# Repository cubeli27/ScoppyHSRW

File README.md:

# Scoppy 

## Overview
Scoppy is an hardware extension project designed to be compatible with the [original Scopy Project](https://github.com/fhdm-dev/scoppy) developed by fhdm-dev. This repository extends the original Raspberry Pi Pico oscilloscope software by providing custom hardware developed as teaching material for the course Design and Manufacturing of Electronics.

The hardware platform enables students to study and manufacture a complete measurement instrument while using the original Scoppy firmware.

<!-- To-do: Add more photos to the list -->

Key Features
- Oscilloscope
- Logic analyzer
- Function generator

---

## Project Structure

| Folder | Description | Contents |
|--------|-------------|-------------|
| **CAD_files** | Case drawings and pcb | .pdf and .step |
| **ECAD_files** | Contains PCB files | Original design and student template  |
| **Images** | Report relevant snippets | Images |
| **Waveforms** | Waveforms Testing Workspace | .dwf3work |

---

## Testing

Images of Scoppy in action.

---
## Firmware

Original project can be found at:<br>
[Github](https://github.com/fhdm-dev/scoppy)<br>
[EasyEDA](https://easyeda.com/editor#id=5d5f637d6a8448b59f484372ed679191)<br>
[Website](https://oscilloscope.fhdm.xyz/)  
 
---
## Getting Started

From the [Scoppy Firmware downloads](https://oscilloscope.fhdm.xyz/wiki/firmware-versions) download and flash the **scoppy-pico-v18.uf2** .

---
## Future Work 
C17 capacitor can be omited or not populated. It is the boot push-button debounce capacitor and in some layouts prevents proper booting persumably because the **RUN** pin is left floating so the code starts running while the capacitor is still charging and before **BOOT** pin reaches logic high. 

---
## Acknowledgements

This project would not have been possible without the original Scoppy software created by the fhdm-dev team. Their work provided the foundation that made this hardware implementation possible.
---
## Author

Developed by **cubeli27** with the support of Frank Kremer (FKR)
For questions or collaboration, feel free to reach out. See my contact info in the [profile repo](https://github.com/cubeli27/cubeli27).

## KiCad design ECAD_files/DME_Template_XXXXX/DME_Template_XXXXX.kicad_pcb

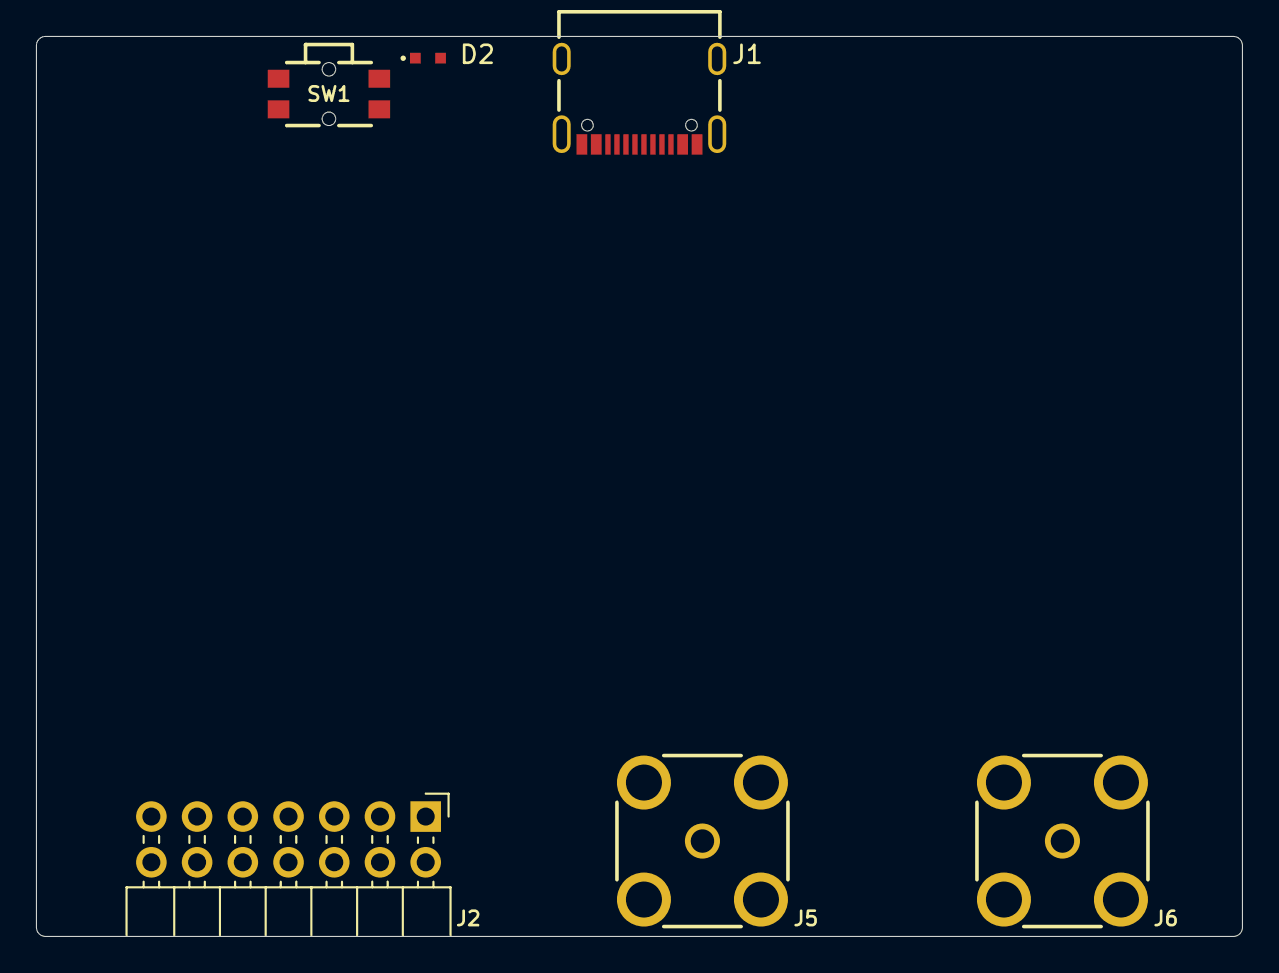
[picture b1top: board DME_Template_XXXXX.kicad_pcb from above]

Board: 4 copper layers, 67.0 x 50.0 mm, 6 parts (0 on the bottom side), 7 nets, no tracks yet.

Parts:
D2: Bright Green, 2V, 140°; WL-SMSW_0603_L1.6W0.98H0.8
J1: 629722000214
J2: Conn_02x07_Odd_Even; PinHeader_2x07_P2.54mm_Horizontal
J5, J6: 60711002241501
SW1: 436351045816

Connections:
/Analog/CH1+: J2.13, J5.1 (Signal)
/Analog/CH2+: J2.11, J6.1 (Signal)
/Digital/~USB_BOOT: SW1.B1, SW1.B2
/Power/unprotectedD+: J1.A6 (D+1), J1.B6 (D+2)
/Power/unprotectedD-: J1.A7 (D-1), J1.B7 (D-2)
GND: D2.1 (K), J1.A1/B12 (GND), J1.A12/B1 (GND), J1.Shell (Shield), J2.12, J2.14, J5.2 (GND), J5.3 (GND), J5.4 (GND), J5.5 (GND), J6.2 (GND), J6.3 (GND), J6.4 (GND), J6.5 (GND), SW1.A1, SW1.A2
VBUS: J1.A4/B9 (VBUS), J1.A9/B4 (VBUS)

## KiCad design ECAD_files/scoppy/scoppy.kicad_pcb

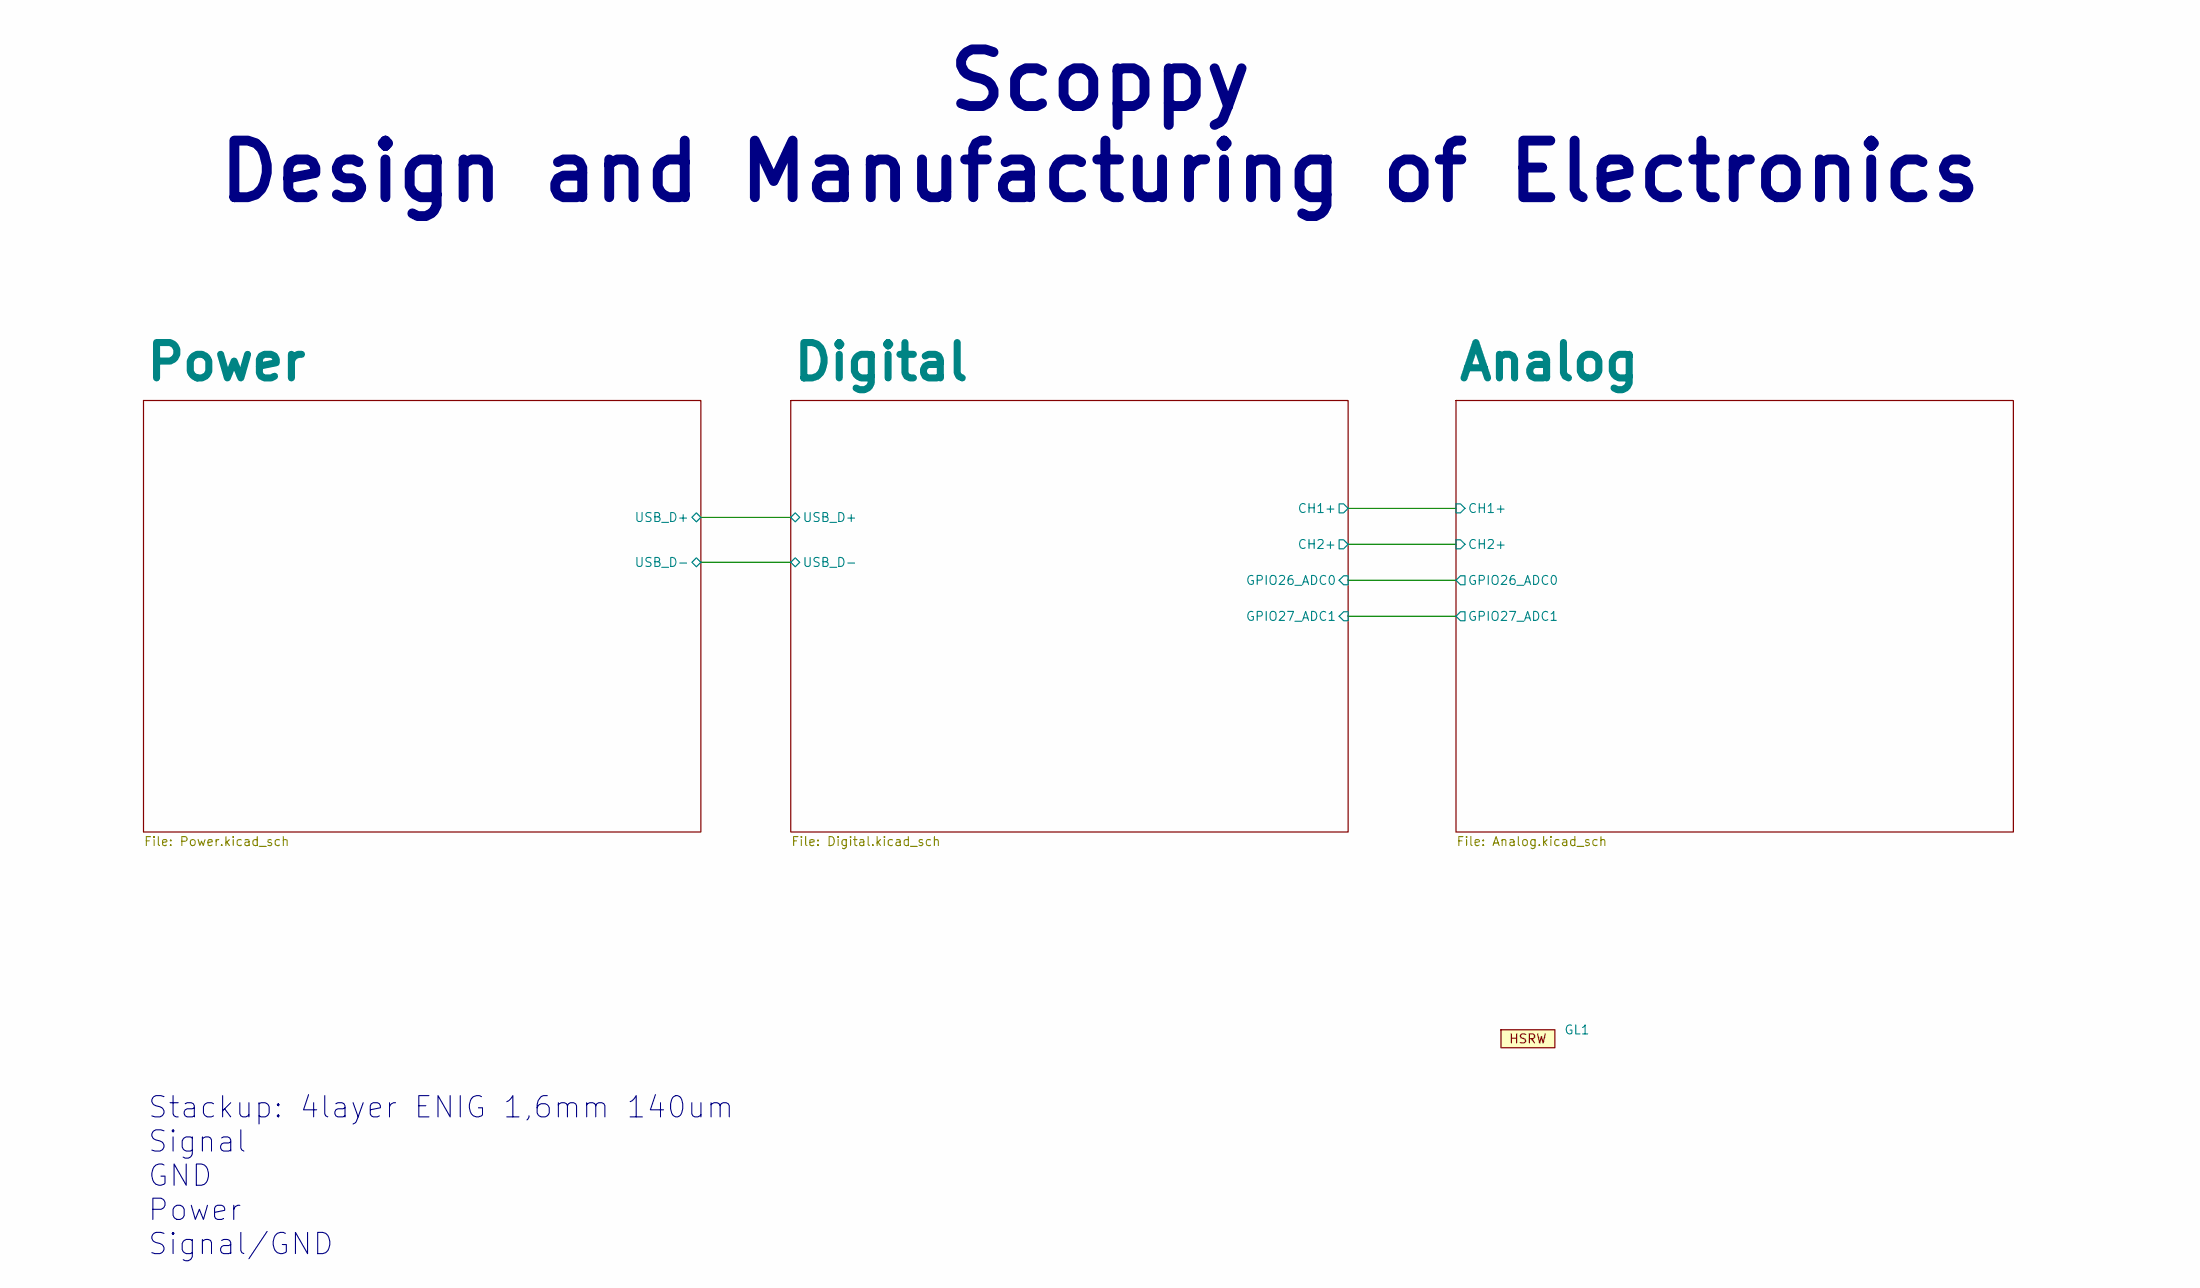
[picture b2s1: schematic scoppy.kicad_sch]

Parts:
GL1: hsrw

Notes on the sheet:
Stackup: 4layer ENIG 1,6mm 140um Signal GND Power Signal/GND
Scoppy Design and Manufacturing of Electronics

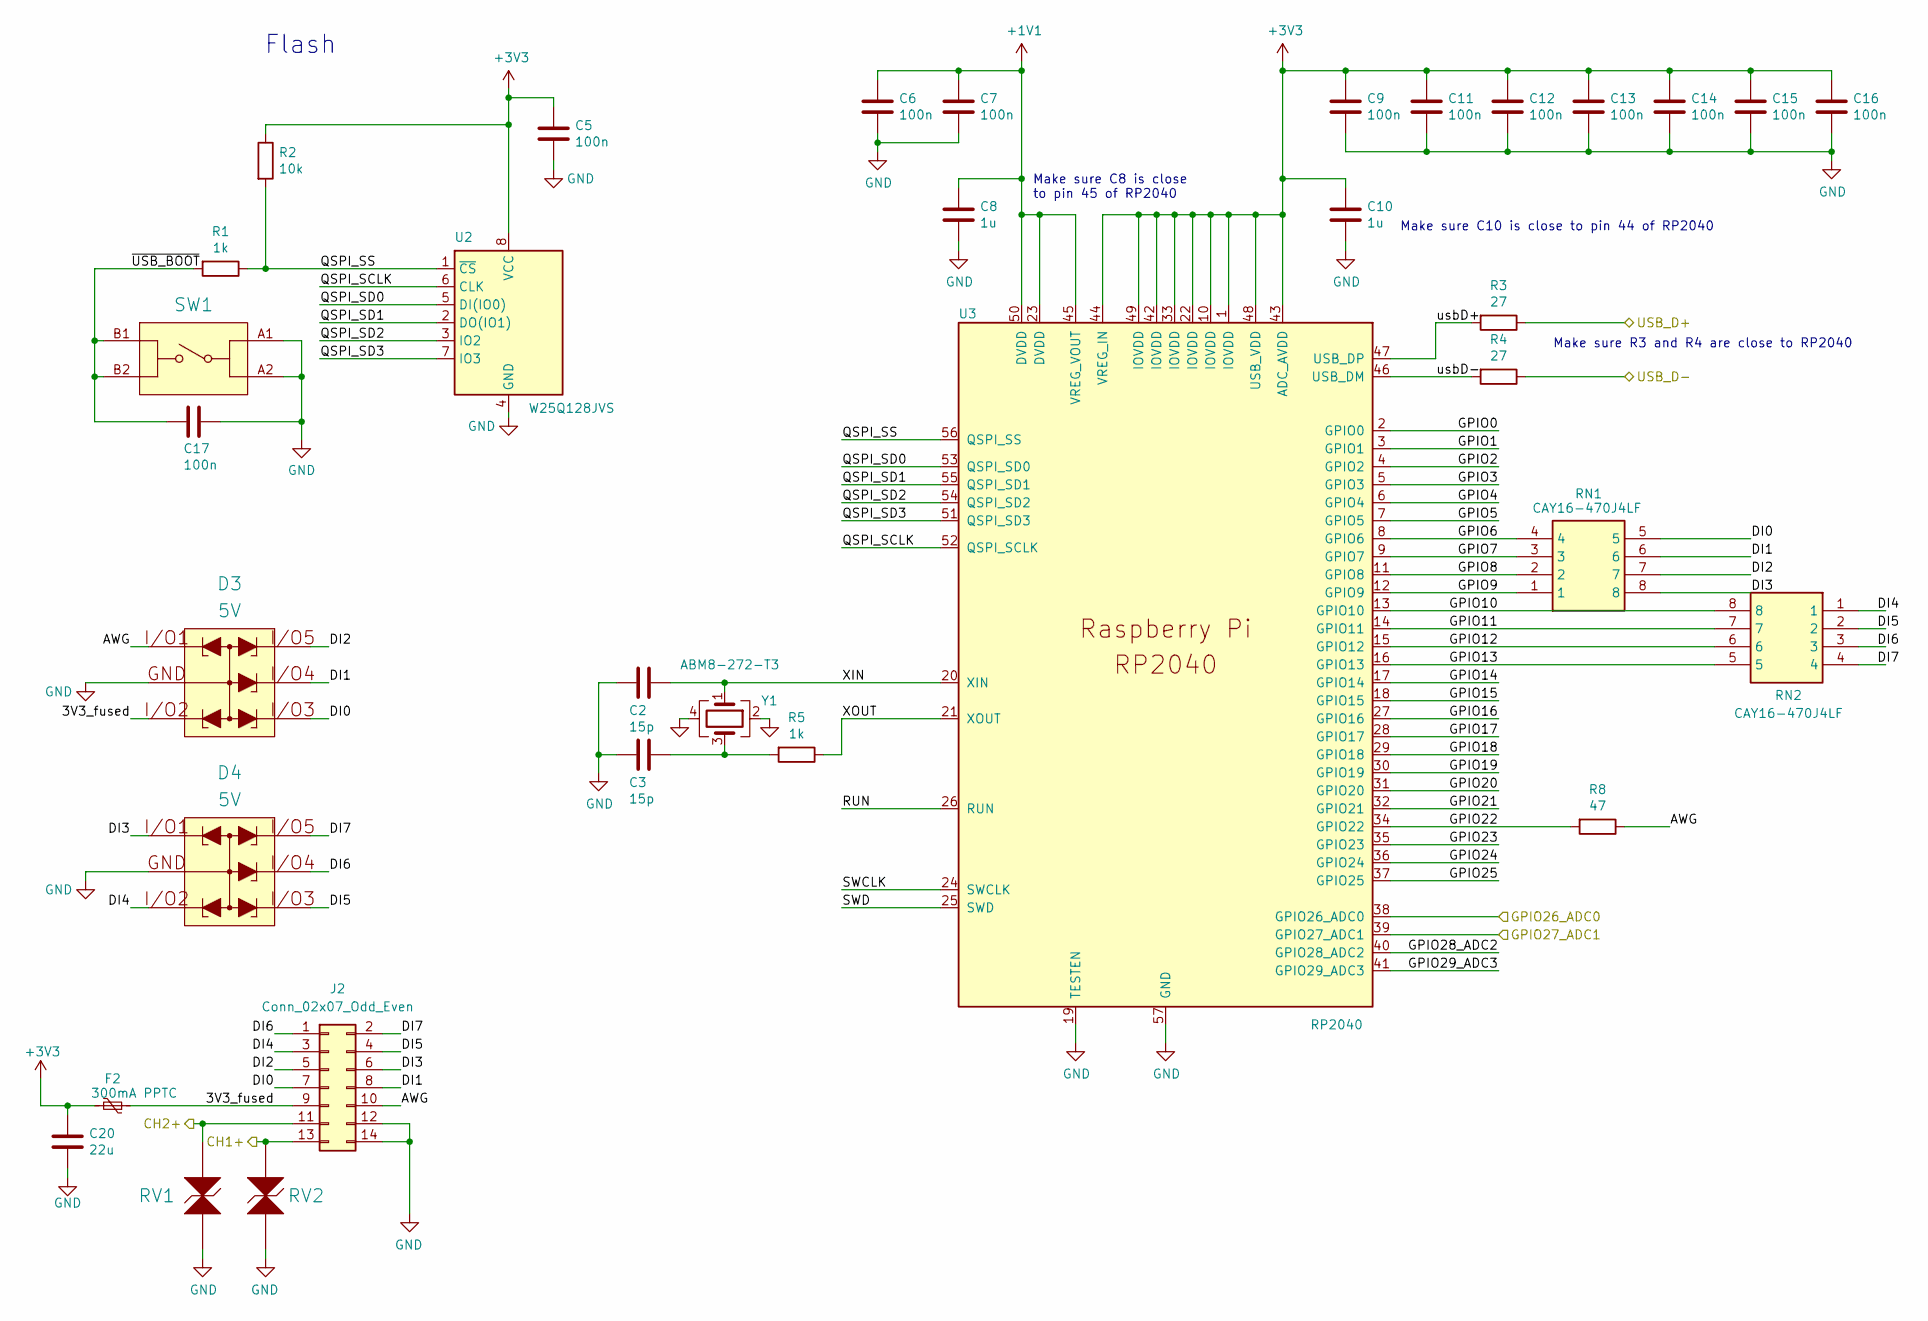
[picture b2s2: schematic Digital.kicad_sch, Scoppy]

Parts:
C2, C3: 15p; C_0603_1608Metric
C5, C6, C7, C9, C11, C12, C13, C14, C15, C16, C17: 100n; C_0603_1608Metric
C8, C10: 1u; C_0603_1608Metric
C20: 22u; C_0603_1608Metric
D3, D4: 5V; WE-TVS_SC70-6L; Manufacturer Part Number 82402375
F2: 300mA PPTC; Fuse_1812_4532Metric
J2: Conn_02x07_Odd_Even; PinHeader_2x07_P2.54mm_Horizontal
R1, R5: 1k; R_0603_1608Metric
R2: 10k; R_0603_1608Metric
R3, R4: 27; R_0603_1608Metric
R8: 47; R_0603_1608Metric
RN1, RN2: CAY16-470J4LF; CAY16470J4LF; Mouser Part Number 652-CAY16-470J4LF
RV1, RV2: 12VDC, 5pF; WE-VE_0603; Clamping Voltage 80V; ESD Voltage 15kV; Manufacturer Part Number 82356120050
SW1: 436351045816; Rated Voltage 12VDC; Manufacturer Part Number 436351045816
U2: W25Q128JVS; WSON-8-1EP_6x5mm_P1.27mm_EP3.4x4.3mm
U3: RP2040; RP2040-QFN-56
Y1: ABM8-272-T3; Crystal_SMD_3225-4Pin_3.2x2.5mm

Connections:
+1V1: C6.1, C7.1, C8.1, U3.23 (DVDD), U3.45 (VREG_VOUT), U3.50 (DVDD)
+3V3: C5.1, C9.1, C10.1, C11.1, C12.1, C13.1, C14.1, C15.1, C16.1, C20.1, F2.2, R2.1, U2.8 (VCC), U3.1 (IOVDD), U3.10 (IOVDD), U3.22 (IOVDD), U3.33 (IOVDD), U3.42 (IOVDD), U3.43 (ADC_AVDD), U3.44 (VREG_IN), U3.48 (USB_VDD), U3.49 (IOVDD); also elsewhere on the board
/Analog/CH1+: J2.13, RV2.2; also elsewhere on the board
/Analog/CH2+: J2.11, RV1.2; also elsewhere on the board
/Analog/GPIO26_ADC0: U3.38 (GPIO26_ADC0); also elsewhere on the board
/Analog/GPIO27_ADC1: U3.39 (GPIO27_ADC1); also elsewhere on the board
/Digital/3V3_fused: D3.3 (I/O_2), F2.1, J2.9
/Digital/AWG: D3.1 (I/O_1), J2.10, R8.1
/Digital/DI0: D3.4 (I/O_3), J2.7, RN1.5
/Digital/DI1: D3.5 (I/O_4), J2.8, RN1.6
/Digital/DI2: D3.6 (I/O_5), J2.5, RN1.7
/Digital/DI3: D4.1 (I/O_1), J2.6, RN1.8
/Digital/DI4: D4.3 (I/O_2), J2.3, RN2.1
/Digital/DI5: D4.4 (I/O_3), J2.4, RN2.2
/Digital/DI6: D4.5 (I/O_4), J2.1, RN2.3
/Digital/DI7: D4.6 (I/O_5), J2.2, RN2.4
/Digital/GPIO0: U3.2 (GPIO0)
/Digital/GPIO1: U3.3 (GPIO1)
/Digital/GPIO2: U3.4 (GPIO2)
/Digital/GPIO3: U3.5 (GPIO3)
/Digital/GPIO4: U3.6 (GPIO4)
/Digital/GPIO5: U3.7 (GPIO5)
/Digital/GPIO6: RN1.4, U3.8 (GPIO6)
/Digital/GPIO7: RN1.3, U3.9 (GPIO7)
/Digital/GPIO8: RN1.2, U3.11 (GPIO8)
/Digital/GPIO9: RN1.1, U3.12 (GPIO9)
/Digital/GPIO10: RN2.8, U3.13 (GPIO10)
/Digital/GPIO11: RN2.7, U3.14 (GPIO11)
/Digital/GPIO12: RN2.6, U3.15 (GPIO12)
/Digital/GPIO13: RN2.5, U3.16 (GPIO13)
/Digital/GPIO14: U3.17 (GPIO14)
/Digital/GPIO15: U3.18 (GPIO15)
/Digital/GPIO16: U3.27 (GPIO16)
/Digital/GPIO17: U3.28 (GPIO17)
/Digital/GPIO18: U3.29 (GPIO18)
/Digital/GPIO19: U3.30 (GPIO19)
/Digital/GPIO20: U3.31 (GPIO20)
/Digital/GPIO21: U3.32 (GPIO21)
/Digital/GPIO22: R8.2, U3.34 (GPIO22)
/Digital/GPIO23: U3.35 (GPIO23)
/Digital/GPIO24: U3.36 (GPIO24)
/Digital/GPIO25: U3.37 (GPIO25)
/Digital/GPIO28_ADC2: U3.40 (GPIO28_ADC2)
/Digital/GPIO29_ADC3: U3.41 (GPIO29_ADC3)
/Digital/QSPI_SCLK: U2.6 (CLK), U3.52 (QSPI_SCLK)
/Digital/QSPI_SD0: U2.5 (DI(IO0)), U3.53 (QSPI_SD0)
/Digital/QSPI_SD1: U2.2 (DO(IO1)), U3.55 (QSPI_SD1)
/Digital/QSPI_SD2: U2.3 (IO2), U3.54 (QSPI_SD2)
/Digital/QSPI_SD3: U2.7 (IO3), U3.51 (QSPI_SD3)
/Digital/QSPI_SS: R1.1, R2.2, U2.1 (~CS), U3.56 (QSPI_SS)
/Digital/RUN: U3.26 (RUN)
/Digital/SWCLK: U3.24 (SWCLK)
/Digital/SWD: U3.25 (SWD)
/Digital/USB_D+: R3.1; also elsewhere on the board
/Digital/USB_D-: R4.1; also elsewhere on the board
/Digital/XIN: C2.1, U3.20 (XIN), Y1.1
/Digital/XOUT: R5.1, U3.21 (XOUT)
/Digital/usbD+: R3.2, U3.47 (USB_DP)
/Digital/usbD-: R4.2, U3.46 (USB_DM)
/Digital/~USB_BOOT: C17.1, R1.2, SW1.B1, SW1.B2
GND: C2.2, C3.2, C5.2, C6.2, C7.2, C8.2, C9.2, C10.2, C11.2, C12.2, C13.2, C14.2, C15.2, C16.2, C17.2, C20.2, D3.2 (GND), D4.2 (GND), J2.12, J2.14, RV1.1, RV2.1, SW1.A1, SW1.A2, U2.4 (GND), U3.19 (TESTEN), U3.57 (GND), Y1.2, Y1.4; also elsewhere on the board
unnamed: C3.1, R5.2, Y1.3

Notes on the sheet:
Make sure C8 is close to pin 45 of RP2040
Flash
Make sure R3 and R4 are close to RP2040
Make sure C10 is close to pin 44 of RP2040

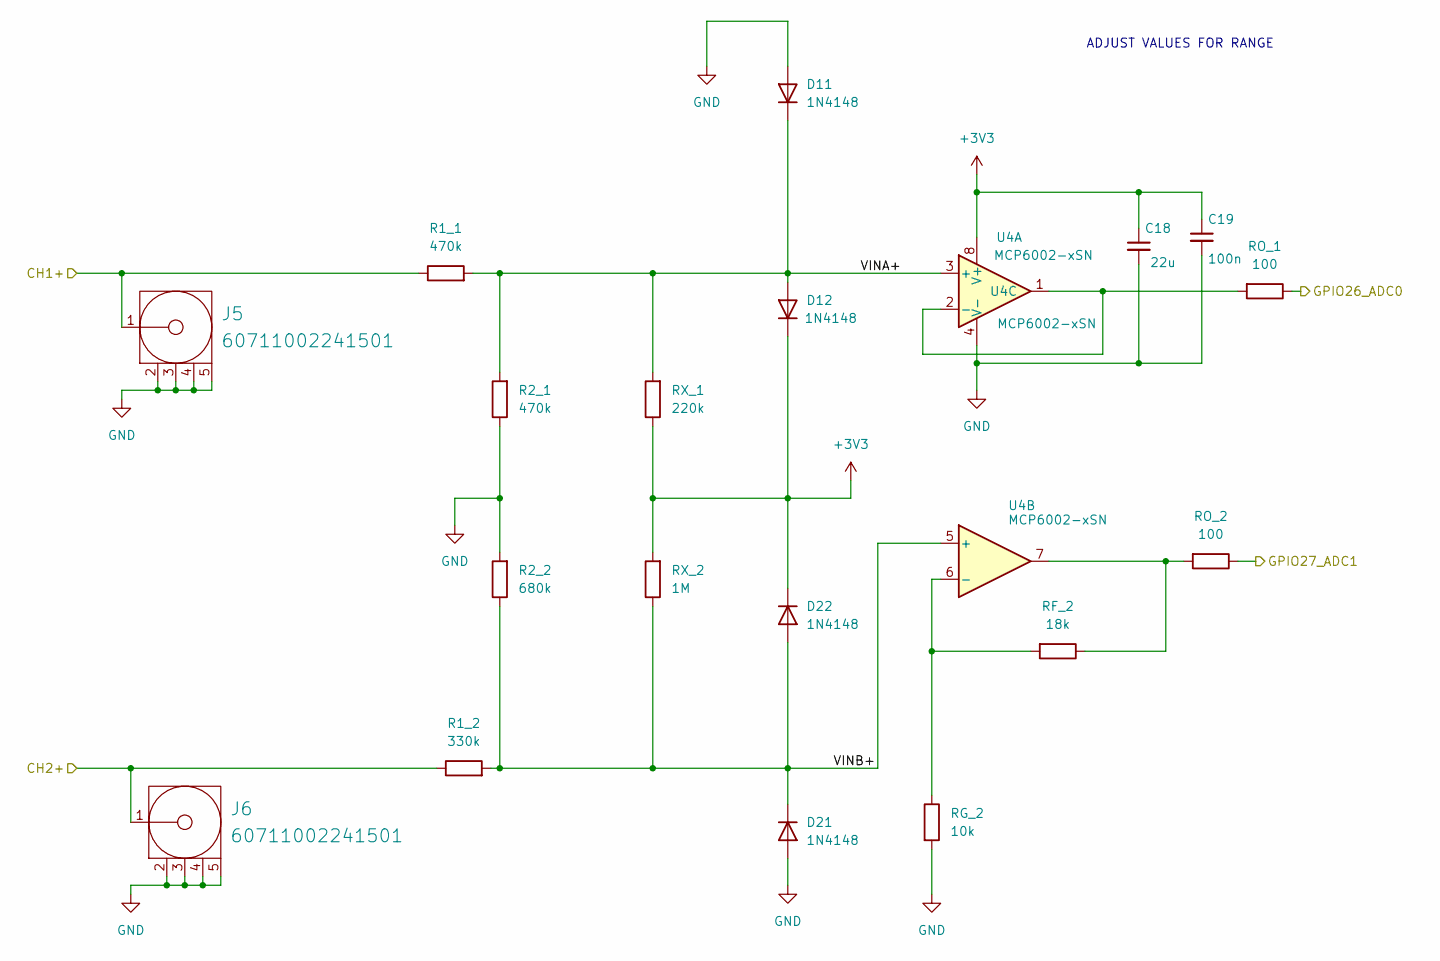
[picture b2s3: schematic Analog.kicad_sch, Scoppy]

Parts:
C18: 22u; C_0603_1608Metric
C19: 100n; C_0603_1608Metric
D11, D12, D21, D22: 1N4148; D_SOD-523
J5, J6: 60711002241501; Manufacturer Part Number 60711002241501
R1_1, R2_1: 470k; R_0603_1608Metric
R1_2: 330k; R_0603_1608Metric
R2_2: 680k; R_0603_1608Metric
RF_2: 18k; R_0603_1608Metric
RG_2: 10k; R_0603_1608Metric
RO_1, RO_2: 100; R_0603_1608Metric
RX_1: 220k; R_0603_1608Metric
RX_2: 1M; R_0603_1608Metric
U4: MCP6002-xSN; SOIC-8_3.9x4.9mm_P1.27mm

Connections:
+3V3: C18.1, C19.1, D12.1 (K), D22.1 (K), RX_1.1, RX_2.2, U4.8 (V+); also elsewhere on the board
/Analog/CH1+: J5.1 (Signal), R1_1.1; also elsewhere on the board
/Analog/CH2+: J6.1 (Signal), R1_2.1; also elsewhere on the board
/Analog/GPIO26_ADC0: RO_1.1; also elsewhere on the board
/Analog/GPIO27_ADC1: RO_2.1; also elsewhere on the board
/Analog/VINA+: D11.1 (K), D12.2 (A), R1_1.2, R2_1.2, RX_1.2, U4.3 (+)
/Analog/VINB+: D21.1 (K), D22.2 (A), R1_2.2, R2_2.1, RX_2.1, U4.5 (+)
GND: C18.2, C19.2, D11.2 (A), D21.2 (A), J5.2 (GND), J5.3 (GND), J5.4 (GND), J5.5 (GND), J6.2 (GND), J6.3 (GND), J6.4 (GND), J6.5 (GND), R2_1.1, R2_2.2, RG_2.2, U4.4 (V-); also elsewhere on the board
unnamed: RF_2.1, RO_2.2, U4.7
unnamed: RO_1.2, U4.1, U4.2 (-)
unnamed: RF_2.2, RG_2.1, U4.6 (-)

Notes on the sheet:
ADJUST VALUES FOR RANGE

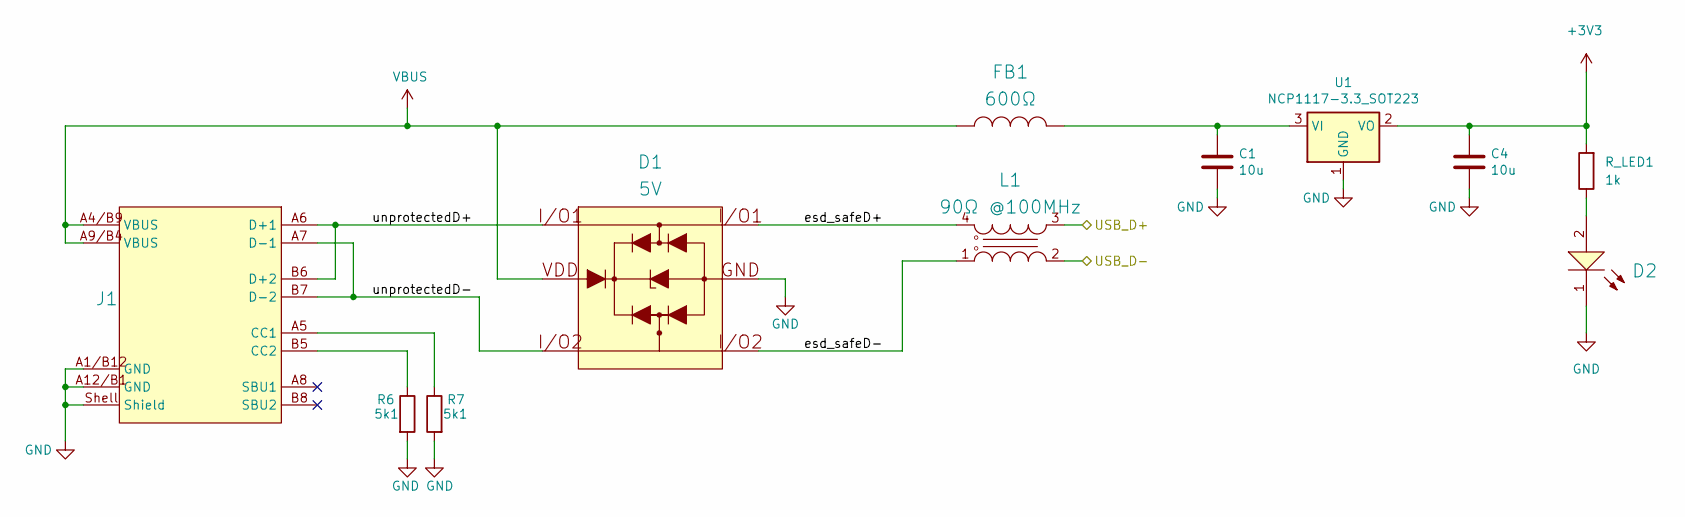
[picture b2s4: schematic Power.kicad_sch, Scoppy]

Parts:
C1, C4: 10u; C_1206_3216Metric
D1: 5V; WE-TVS_SOT23-6L; Manufacturer Part Number 82400102
D2: Bright Green, 2V, 140°; WL-SMSW_0603_L1.6W0.98H0.8; Forward Voltage 2V; Manufacturer Part Number 155060VS75300
FB1: 600Ω; WE-CBF_0603_L1.6W0.8H0.8_HC; Manufacturer Part Number 742792651
J1: 629722000214; Working Voltage 48V (DC); Manufacturer Part Number 629722000214
L1: 90Ω @100MHz; WE-CNSW_1206; Rated Voltage 50V; Manufacturer Part Number 744232090
R6, R7: 5k1; R_0603_1608Metric
R_LED1: 1k; R_0603_1608Metric
U1: NCP1117-3.3_SOT223; SOT-223-3_TabPin2

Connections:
+3V3: C4.1, R_LED1.2, U1.2 (VO); also elsewhere on the board
/Digital/USB_D+: L1.3; also elsewhere on the board
/Digital/USB_D-: L1.2; also elsewhere on the board
/Power/esd_safeD+: D1.1 (I/O_1), L1.4
/Power/esd_safeD-: D1.3 (I/O_2), L1.1
/Power/unprotectedD+: D1.6 (I/O_1), J1.A6 (D+1), J1.B6 (D+2)
/Power/unprotectedD-: D1.4 (I/O_2), J1.A7 (D-1), J1.B7 (D-2)
GND: C1.2, C4.2, D1.2 (GND), D2.1 (K), J1.A1/B12 (GND), J1.A12/B1 (GND), J1.Shell (Shield), R6.2, R7.2, U1.1 (GND); also elsewhere on the board
unnamed: D2.2 (A), R_LED1.1
unnamed: J1.A5 (CC1), R7.1
unnamed: J1.B5 (CC2), R6.1
unnamed: C1.1, FB1.2, U1.3 (VI)
VBUS: D1.5 (VDD), FB1.1, J1.A4/B9 (VBUS), J1.A9/B4 (VBUS)

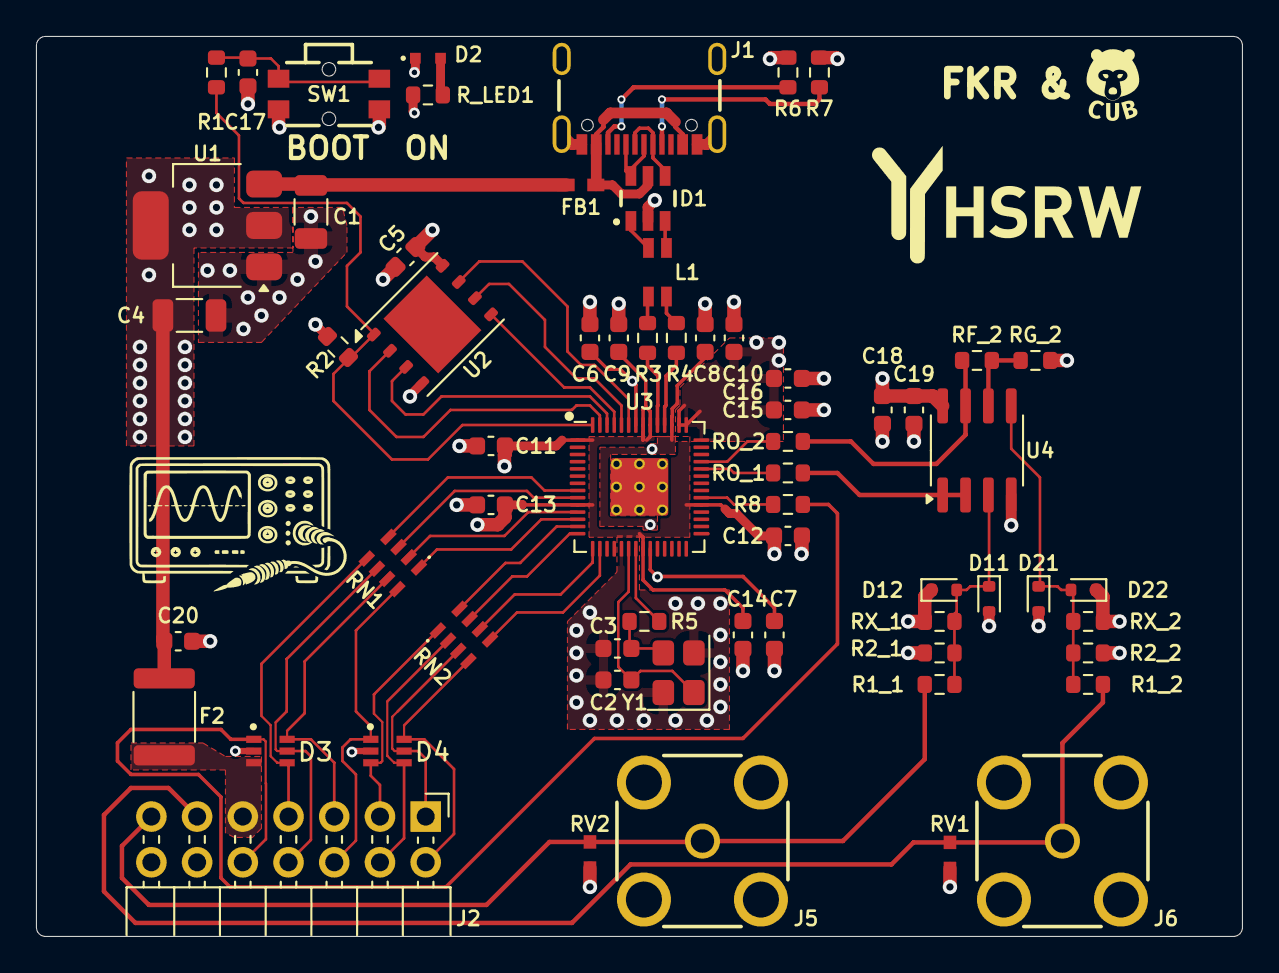
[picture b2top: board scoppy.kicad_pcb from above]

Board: 4 copper layers, 67.0 x 50.0 mm, 65 parts (0 on the bottom side), 54 nets.
